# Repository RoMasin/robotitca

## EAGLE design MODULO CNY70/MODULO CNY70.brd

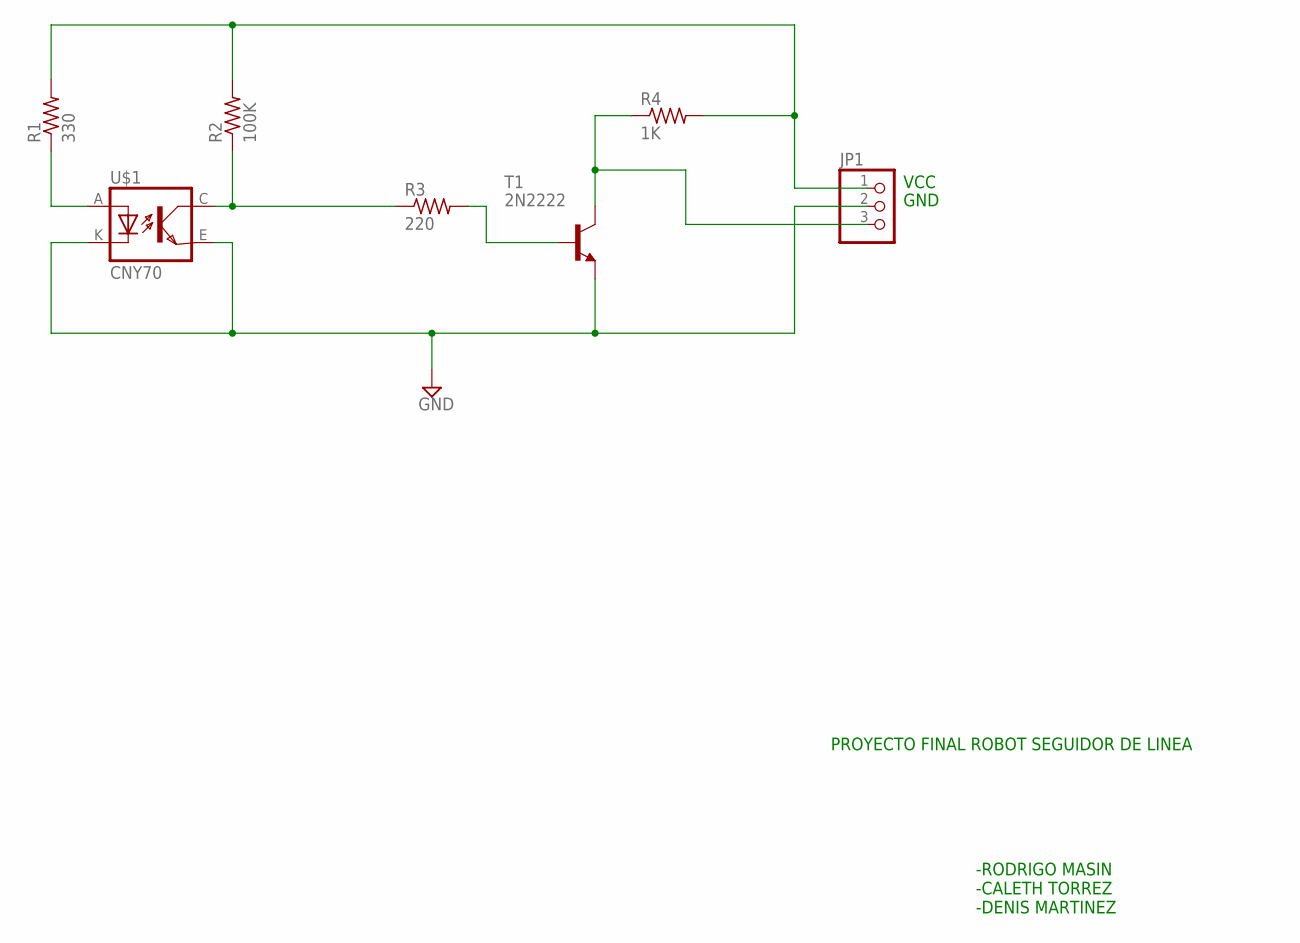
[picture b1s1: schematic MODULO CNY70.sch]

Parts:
JP1: PINHD-1X3; 1X03
R1: 330; 0207/7
R2: 100K; 0207/7
R3: 220; 0207/7
R4: 1K; 0207/7
T1: 2N2222; TO18
U$1: CNY70; 4

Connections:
unnamed: R1.1, U$1.A
unnamed: R2.1, R3.1, U$1.C (COL)
unnamed: JP1.1, R1.2, R2.2, R4.2
unnamed: JP1.2, T1.1 (E), U$1.E (EMI), U$1.K (C)
unnamed: R3.2, T1.2 (B)
unnamed: JP1.3, R4.1, T1.3 (C)

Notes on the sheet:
PROYECTO FINAL ROBOT SEGUIDOR DE LINEA
-RODRIGO MASIN -CALETH TORREZ -DENIS MARTINEZ
GND
VCC

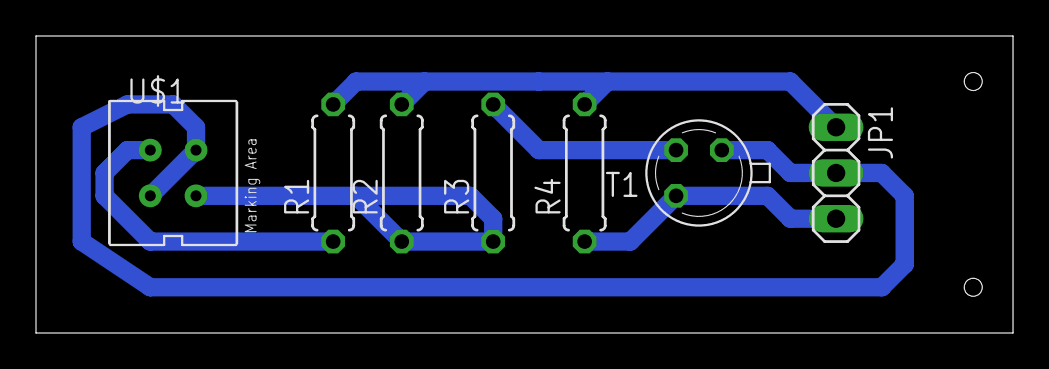
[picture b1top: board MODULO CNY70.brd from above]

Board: 2 copper layers, 54.3 x 16.5 mm, 7 parts (0 on the bottom side), 6 nets.

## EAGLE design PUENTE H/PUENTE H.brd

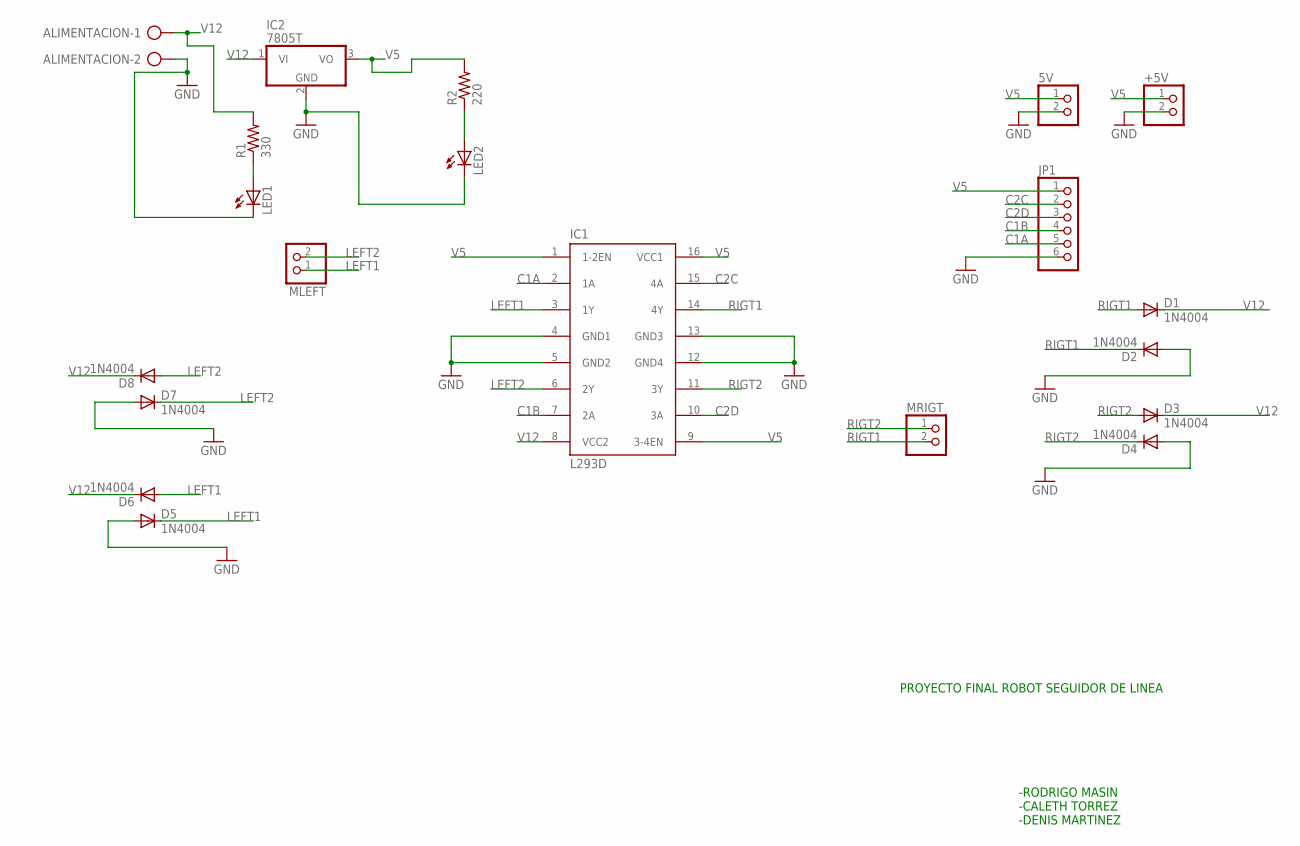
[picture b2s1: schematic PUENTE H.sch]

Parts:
5V: PINHD-1X2; 1X02
+5V: PINHD-1X2; 1X02
ALIMENTACION: AK500/2-H
D1, D2, D3, D4, D5, D6, D7, D8: 1N4004; DO41-10
IC1: L293D; DIL16
IC2: 7805T; TO220H
JP1: PINHD-1X6; 1X06
LED1, LED2: LED5MM
MLEFT: PINHD-1X2; 1X02
MRIGT: PINHD-1X2; 1X02
R1: 330; 0204/7
R2: 220; 0204/7

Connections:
C1A: IC1.2 (1A), JP1.5
C1B: IC1.7 (2A), JP1.4
C2C: IC1.15 (4A), JP1.2
C2D: IC1.10 (3A), JP1.3
GND: 5V.2, +5V.2, ALIMENTACION.2, D2.A, D4.A, D5.A, D7.A, IC1.4 (GND1), IC1.5 (GND2), IC1.12 (GND4), IC1.13 (GND3), IC2.2 (GND), JP1.6, LED1.K (C), LED2.K (C)
LEFT1: D5.C, D6.A, IC1.3 (1Y), MLEFT.1
LEFT2: D7.C, D8.A, IC1.6 (2Y), MLEFT.2
unnamed: LED1.A, R1.1
unnamed: LED2.A, R2.1
RIGT1: D1.A, D2.C, IC1.14 (4Y), MRIGT.2
RIGT2: D3.A, D4.C, IC1.11 (3Y), MRIGT.1
V5: 5V.1, +5V.1, IC1.1 (1-2EN), IC1.9 (3-4EN), IC1.16 (VCC1), IC2.3 (VO), JP1.1, R2.2
V12: ALIMENTACION.1, D1.C, D3.C, D6.C, D8.C, IC1.8 (VCC2), IC2.1 (VI), R1.2

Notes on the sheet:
PROYECTO FINAL ROBOT SEGUIDOR DE LINEA
-RODRIGO MASIN -CALETH TORREZ -DENIS MARTINEZ

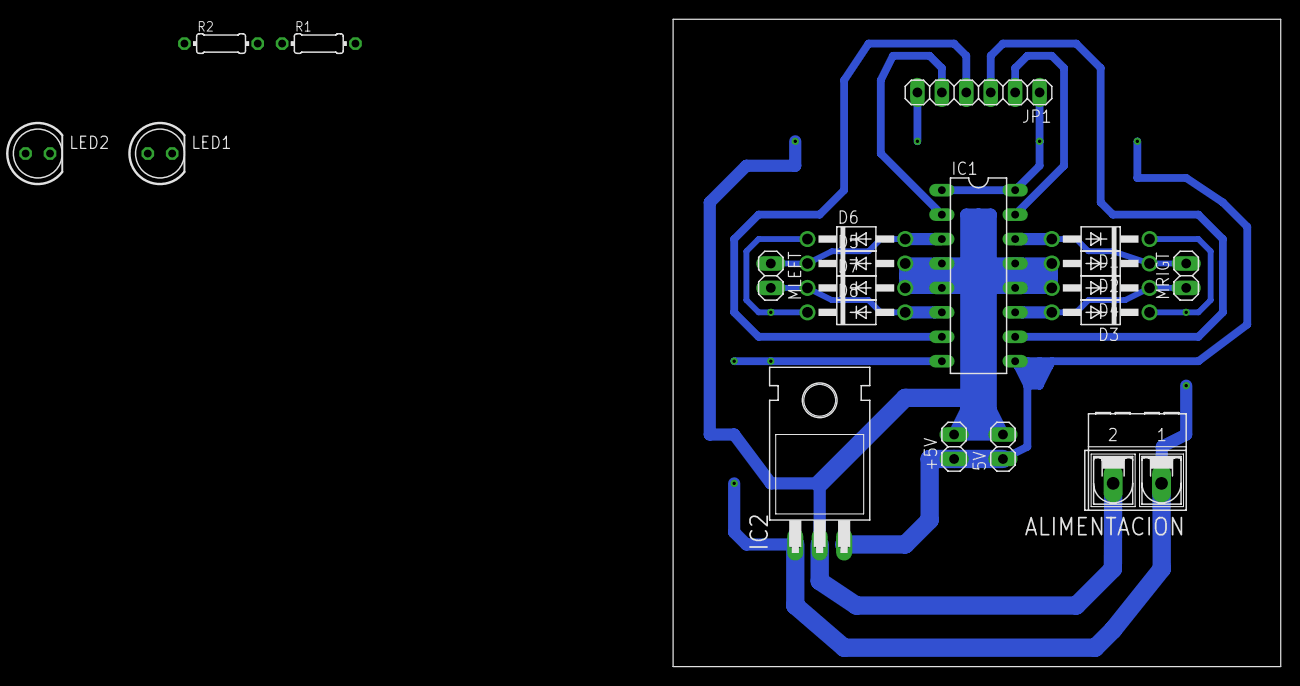
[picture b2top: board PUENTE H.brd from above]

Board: 2 copper layers, 63.2 x 67.3 mm, 20 parts (0 on the bottom side), 13 nets.

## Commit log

2018-05-20 prueba de comit
2018-05-20 e agregaron diseÃ±os de circuitos y chasis
2018-05-20 Eagregaron los pdf de los circuitos y chasis
2018-06-13 archivos actualizados
2018-10-17 granja inteligente
2018-11-13 ieee_paper_granjainteligente.pdf
